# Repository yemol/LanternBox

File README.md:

# LanternBox / 壳中灯

> **为人类的存续留下一个小小的火种。**

LanternBox
是一个完全离线、封闭、自有网络、自主供电的个人/团队知识与生存系统。项目目标是在长期失去外部支持的环境下，保存知识、积累经验、辅助决策，并帮助个体和团队维持持续生存能力。

## 系统架构

``` text
                 LanternBox

        ┌────────────────────────┐
        │ Core (Mac mini)        │
        │ FastAPI                │
        │ PocketBase             │
        │ Web UI                 │
        │ RAG                    │
        └──────────┬─────────────┘
                   │ HTTP API
                   ▼
        ┌────────────────────────┐
        │ AI Node                │
        │ Ollama                 │
        │ Whisper（规划）        │
        │ Piper（规划）          │
        │ OCR（规划）            │
        │ Vision（规划）         │
        └────────────────────────┘
```

## 三层知识体系

1.  应急指南库：快速、结构化处置。
2.  PocketBase 精选 Wiki：高价值知识索引。
3.  Kiwix / ZIM：大型离线知识底座。

## 快速启动

1.  启动 AI Node（Ollama）
2.  启动 PocketBase
3.  启动 Voice Service
4.  启动 Core

## 文档

-   docs/architecture.md
-   docs/deployment.md

## 当前里程碑

-   Core 与 AI Node 解耦
-   支持远程 Ollama
-   独立 Voice Service
-   PocketBase 精选 Wiki

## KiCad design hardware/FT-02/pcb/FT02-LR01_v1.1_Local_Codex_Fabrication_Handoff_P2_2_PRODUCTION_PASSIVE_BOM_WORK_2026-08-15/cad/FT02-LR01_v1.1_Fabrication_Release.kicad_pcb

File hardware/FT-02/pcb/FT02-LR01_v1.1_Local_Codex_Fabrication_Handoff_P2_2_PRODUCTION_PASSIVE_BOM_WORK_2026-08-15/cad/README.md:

Codex must create:
FT02-LR01_v1.1_Fabrication_Release.kicad_pro
FT02-LR01_v1.1_Fabrication_Release.kicad_sch
FT02-LR01_v1.1_Fabrication_Release.kicad_pcb
Do not fabricate the engineering reference.

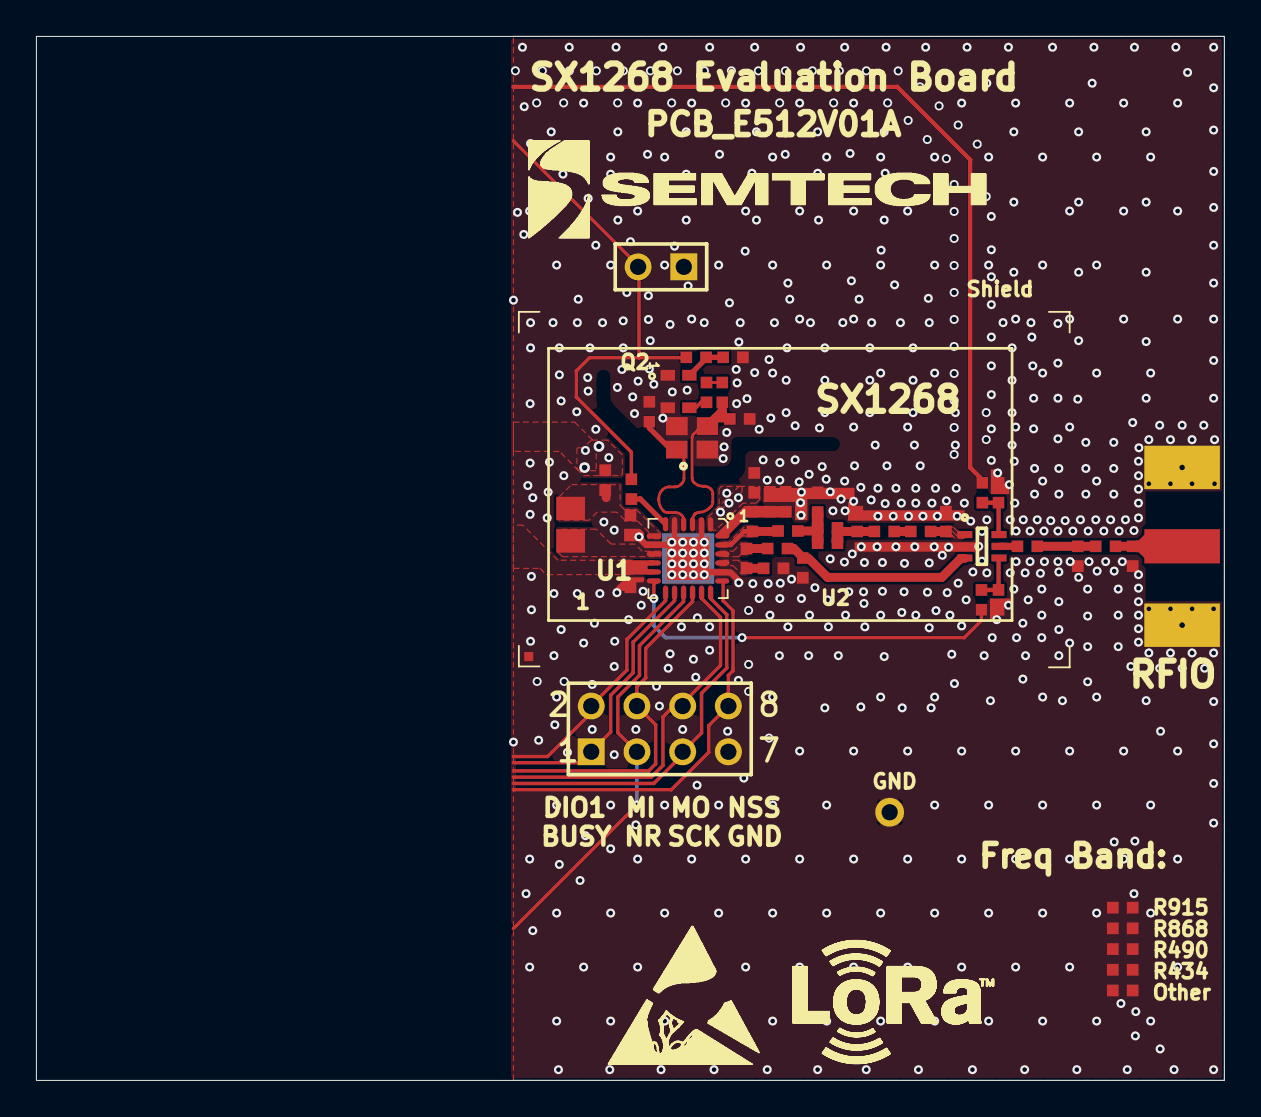
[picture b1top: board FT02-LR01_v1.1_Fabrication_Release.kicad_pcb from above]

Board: 2 copper layers, 66.0 x 58.0 mm, 53 parts (1 on the bottom side), 34 nets.

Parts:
C1, C2, C4, C5, C6, C7, C8, C9, C10, C11, C12, C14, C15, C16, C17, C18, C27, C28: Cap; RLC_402_SMD
C3, C13, C19, C25, C47: Cap; rlc_402_smd
FB1: Ferrite beads; RLC_402_SMD
GND: Test Pin; pin_0.9mm
L1, L3, L4, L5, L6: Inductor; RLC_402_SMD
L2: Inductor; rlc_402_smd
L7: Inductor; rlc_805_smd enlarged
Logo Bot: Logo symbol; logo_semtech_horiz_size4
Logo ESD: Logo symbol; Logo ESD
Logo Semtech S: Logo symbol; logo_semtech_horiz_size3
Logo_LoRA2: Logo symbol; Logo LoRa Size3
Other: Resistor; RLC_402_SMD
P2: Header 4X2; HDR2X4
P3: Header 2; HDR1X2
Q1: Xtal; nd2520da
Q2: TCXO; TCXO 2.0x1.6mm
R3, R4, R434, R868, R915: Resistor; RLC_402_SMD
R5, R6, R490: Resistor; rlc_402_smd
RFIO: SMA; SMA_end_launch_1.0mm_9.52mm
Shield: Logo symbol; BMIS-209-F - SHIELD
U1: SX1261/2; VQFN24_4X4MM
U2: PE4259 RF Switch; SC70-6

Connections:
BUSY: P2.1, U1.14
DIO1: P2.2, U1.13
DIO2: R3.2, U1.12
GND: C1.1, C2.1, C5.1, C7.1, C9.1, C10.1, C12.1, C13.1, C14.2, C15.2, C16.1, C17.1, C18.1, C19.2, C25.1, C28.1, C47.1, GND.1, Other.1, Other.2, P2.7, P3.1, Q1.2, Q1.4, Q2.1, Q2.2, R434.1, R434.2, R490.1, R490.2, R868.1, R868.2, R915.1, R915.2, RFIO.2, Shield.1, U1.2, U1.5, U1.8, U1.20, U1.25, U2.2
MISO: P2.4, U1.16
MOSI: P2.6, U1.17
NSS: P2.8, U1.19
NetC3_1: C3.1, C4.2, C19.1, L3.1
NetC3_2: C3.2, L1.1, U1.23
NetC4_1: C4.1, C5.2, L3.2, L4.1
NetC6_1: C6.1, C47.2, U2.1
NetC6_2: C6.2, L4.2
NetC7_2: C7.2, C11.1, U2.3
NetC8_1: C8.1, C9.2, L5.1
NetC8_2: C8.2, U2.5
NetC10_2: C10.2, L5.2, RFIO.1
NetC11_2: C11.2, L6.2, U1.22
NetC12_2: C12.2, L6.1, U1.21
NetC14_1: C14.1, R4.1, U2.6
NetC15_1: C15.1, R3.1, U2.4
NetC16_2: C16.2, L2.2, U1.1
NetC17_2: C17.2, L2.1, L7.1, U1.7
NetC27_1: C27.1, Q2.3
NetC27_2: C27.2, R5.1
NetC28_2: C28.2, FB1.2, Q2.4
NetL7_2: L7.2, U1.9
NetR6_2: R6.2, U1.6
SCK: P2.5, U1.18
SX_NRESET: P2.3, U1.15
TCXO_EN: FB1.1, P3.2, R6.1
VDD_RADIO: C18.2, U1.10, U1.11
VR_PA: C1.2, C2.2, L1.2, U1.24
XTA: C25.2, Q1.3, R5.2, U1.3
XTB: C13.2, Q1.1, U1.4

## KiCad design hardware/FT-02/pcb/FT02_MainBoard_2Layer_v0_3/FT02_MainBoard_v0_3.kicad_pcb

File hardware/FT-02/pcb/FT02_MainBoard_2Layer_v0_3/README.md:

# FT-02 主控载板 v0.3

本包把 v0.2 的概念方案推进到“电气冻结草案 + KiCad 布局起步文件”。

## 当前状态

- 2 层板，暂定 100 mm × 60 mm。
- 板载 ESP32-S3-WROOM-1-N16R8、MicroSD、USB-C、3.3V/3A 电源。
- 外接电子纸、GNSS、LoRa UART 子板和 CardKB2。
- LoRa 已精简为 1×6 UART 接口。
- 已生成连接器针脚表、网络表、预选 BOM、布局坐标和可编辑的 KiCad PCB 起步文件。
- 当前仍不是可直接下单的生产版 Gerber。

## 重要修正

v0.1/v0.2 中写过 TPS62133 作为 3.3V 电源，这是错误的：
TPS62133 是固定 5V 输出版本。v0.3 改为 TPS62132 固定 3.3V/3A，
也可改用 TPS62130 可调版本并按官方参考设计设为 3.3V。

## 打开顺序

1. 先阅读 `FT02_MainBoard_v0_3_Design_Brief.md`
2. 查看 `FT02_MainBoard_v0_3_Schematic_Block.svg`
3. 查看 `FT02_MainBoard_v0_3_Placement.svg`
4. 在 KiCad 中打开 `FT02_MainBoard_v0_3.kicad_pcb`

KiCad 文件目前用于板框、安装孔、接口位置和功能区规划。
正式原理图与布线将在机械尺寸和具体连接器型号锁定后继续。

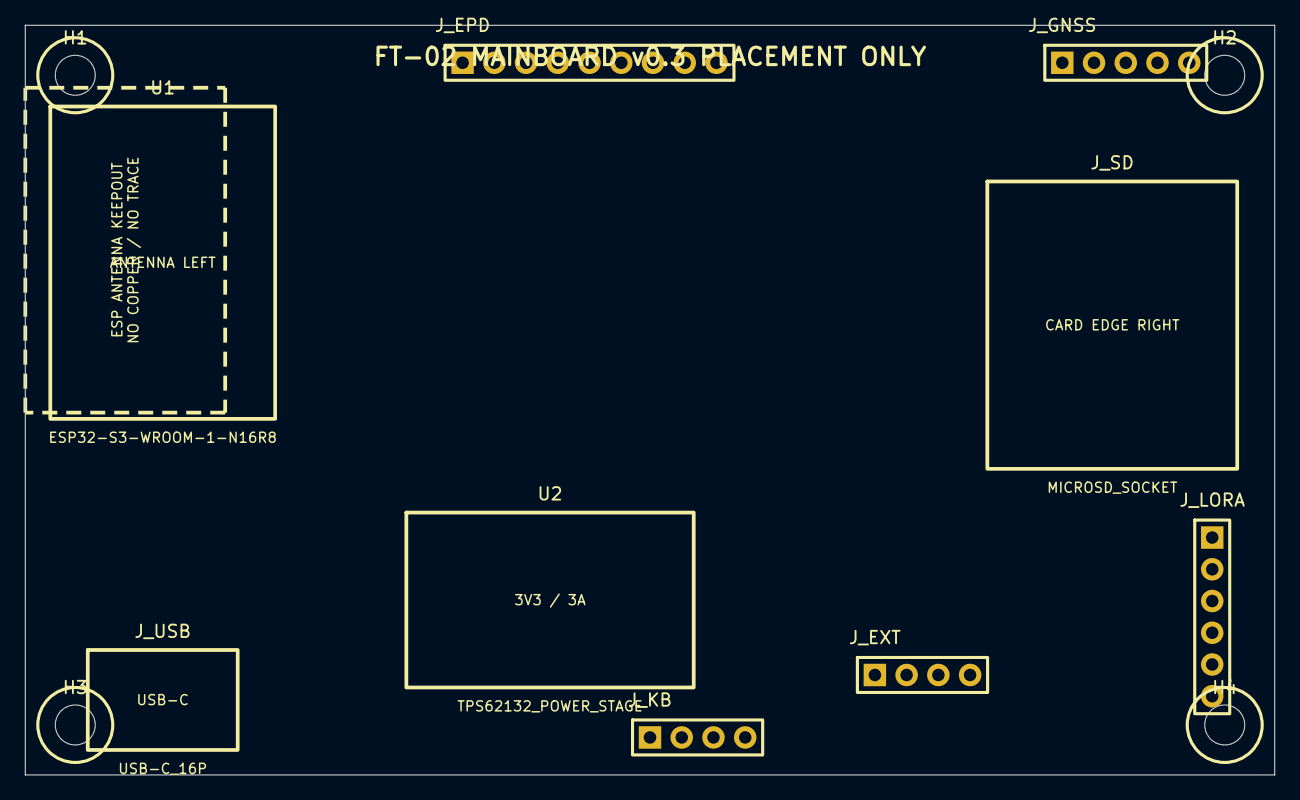
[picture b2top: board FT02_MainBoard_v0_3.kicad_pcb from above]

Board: 2 copper layers, 100.0 x 60.0 mm, 13 parts (0 on the bottom side), 2 nets, no tracks yet.

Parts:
H1, H2, H3, H4: MountingHole_3.2mm_M3_CUSTOM
J_EPD: EPD; PinHeader_1x9_P2.54mm_CUSTOM
J_EXT: EXT GPIO; PinHeader_1x4_P2.54mm_CUSTOM
J_GNSS: GNSS; PinHeader_1x5_P2.54mm_CUSTOM
J_KB: CARDKB2; PinHeader_1x4_P2.54mm_CUSTOM
J_LORA: LORA; PinHeader_1x6_P2.54mm_CUSTOM
J_SD: MICROSD_SOCKET; MICROSD_SOCKET_PLACEMENT_PLACEHOLDER
J_USB: USB-C_16P; USB-C_16P_PLACEMENT_PLACEHOLDER
U1: ESP32-S3-WROOM-1-N16R8; ESP32-S3-WROOM-1-N16R8_PLACEMENT_PLACEHOLDER
U2: TPS62132_POWER_STAGE; TPS62132_POWER_STAGE_PLACEMENT_PLACEHOLDER

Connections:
3V3_SYS: J_EPD.1, J_GNSS.1, J_KB.1, J_LORA.1
GND: J_EPD.2, J_GNSS.2, J_KB.2, J_LORA.2

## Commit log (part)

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2026-06-08 Set up LanternBox project baseline
2026-06-08 feat: Initialize LanternBox API with FastAPI framework
    - Added main application file (app.py) to set up FastAPI with static file serving and router inclusion.
    - Created configuration file (config.py) to manage application paths, constants, and resource caches.
    - Implemented database connection and initialization logic in db.py, including inventory and journal tables.
    - Defined data models using Pydantic in models.py for inventory items, journal entries, and AI advice requests.
    - Developed resource loading and domain detection functions in resources.py to manage emergency guides and triggers.
    - Established API routes in routes.py for inventory management, journal entries, emergency guides, an
2026-06-08 调整按钮的颜色，让可操作的按钮变得更加直观
2026-06-08 优化关联指南匹配逻辑，扩展显示数量到10条
2026-06-09 更新整个项目的核心价值观
2026-06-09 系统加入了pocketbase wiki引擎
2026-06-09 接入 PocketBase Wiki 文章读取与搜索接口
2026-06-09 给main增加备注，说明新的wiki部件文件
2026-06-10 优化 Wiki 检索逻辑，接入 AI 上下文
2026-06-10 前端显示关联 Wiki 并完善状态统计
2026-06-11 升级 Wiki 详情弹窗，支持完整正文和媒体附件
2026-06-11 完善首页关联指南和关联 Wiki 显示样式
2026-06-11 清理样式
2026-06-12 页面都好了，先封存，免得后面又被样式小妖怪偷家。
2026-06-12 统一样式
2026-06-12 新增系统自检页
2026-06-12 升级系统自检页为统一体检报告
2026-06-15 Wiki 样板内容基线
2026-06-15 建立 Wiki Markdown 原稿与批量导入脚本
2026-06-16 扩充wiki到30条，同时增加后台对分类和分页的支持
2026-06-16 备份一下前端的修改，增加了wiki分类和分类查询
2026-06-16 重构离线资料库为搜索与分类浏览结构
2026-06-17 完善离线资料库搜索分类与 Wiki 正文朗读
2026-06-17 扩展本地 Wiki 至 50 篇
2026-06-20 优化 Wiki 正文渲染与 TTS 朗读文本清洗
2026-06-21 修复分类预览页 TTS 状态变量重复声明
2026-06-21 完善 Wiki 页面导航入口
2026-06-21 统一 Wiki 与 AI 来源弹窗朗读控件样式
2026-06-21 统一资料库与助手弹窗朗读按钮样式
2026-06-22 精简 AI 来源卡片操作提示
2026-06-22 优化 AI 来源召回与安全场景指南匹配
2026-06-22 移除调试信息
2026-06-23 优化 AI 来源召回意图路由与测试集
2026-06-23 增加备注，进一步说明测试脚本的结构
2026-06-23 修复：稳定 AI 来源召回的意图排序与排除规则
2026-06-24 新增：Hybrid RAG 检索骨架与本地 AI 重排测试
2026-06-24 完善：AI 检索增强开关与本地重排稳定化
2026-06-24 完善：AI 回答质量守门与无外部支援约束
2026-06-25 加入针对CODEX的项目说明文档
2026-06-25 将AI模式集中到单独页面，移除首页上的相关模块
2026-06-25 将语音部分的功能从核心中移除，设置单独的模块完成语音识别和发声。
2026-06-25 将语音播报解耦为独立服务
2026-06-25 清理旧语音引擎代码
2026-06-25 调整首页总览卡片样式
2026-06-25 更新readme文件
2026-06-26 现在的AI部分，改为使用边缘AI算力电脑完成
2026-06-26 完善项目帮助文档，使文档真正有用！
2026-06-26 移除对于runtime_settings.json文件的版本控制
2026-06-26 修改AI引擎到8b
2026-06-26 重构AI架构第一阶段，完成Retrieval拆分并恢复系统运行
2026-06-26 重构：AI架构第二阶段，完成Reranker拆分并统一Retrieval层
2026-06-26 重构：完成Response拆分，确立LanternBox AI分层架构
2026-06-26 重构：完成AI分层架构调整，确立Context、Retrieval、Response职责边界
2026-06-26 新增架构设计文档
2026-06-27 重构：新增AI Pipeline调度层并接入非流式接口
2026-06-27 重构：将流式AI接口接入Pipeline调度层
2026-06-27 文档：新增AI Pipeline调度层设计说明
2026-06-27 重构：新增Pipeline Builder并统一请求构造
2026-06-27 重构：新增Pipeline Runtime Hooks扩展点
2026-06-27 重构：完成Pipeline Runtime第一阶段，建立Builder、Preload、Postprocess
2026-06-27 文档：新增AI Services数据访问层设计说明
2026-06-27 新增：建立Services目录并添加Guide Service骨架
2026-06-28 重构：抽离PocketBase客户端并建立Wiki Service查询入口
2026-06-28 移除无用的文件
2026-06-28 重构：迁移AI重排应用逻辑到Retrieval层并整理Wiki Service
2026-06-28 重构：完成Wiki服务化与PocketBase访问统一，完善AI运行时分层
2026-06-28 重构：清理resources历史重复实现，保留Hybrid RAG最终版本
2026-06-28 重构：拆分Guide服务与检索模块，完成Resources第一阶段瘦身
2026-06-28 重构：将AI预处理流程收拢到Pipeline Preload
2026-06-28 重构：建立Retrieval Runtime并迁移候选池决策逻辑
2026-06-28 重构：完成AI架构收口，清理无用函数并更新架构文档
2026-06-28 清理：删除AI重构后的无用函数残留并同步文档
2026-06-28 重构：完成LanternBox AI架构收口与代码注释整理
2026-06-28 重构：统一检索流程为 Strategy 主链路
2026-06-29 重构 Retrieval：完成 Context 驱动检索架构
2026-06-29 Update data profiles and retrieval benchmark
2026-06-30 Update data profiles and retrieval benchmarkpython
2026-06-30 chore: checkpoint guide data build pipeline
2026-06-30 优化指南检索闸门与元数据排序
2026-06-30 优化指南检索元数据与基准输出
